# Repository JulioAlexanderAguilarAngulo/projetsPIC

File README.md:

projetsPIC
==========

Pic Microcontroller Based Projects

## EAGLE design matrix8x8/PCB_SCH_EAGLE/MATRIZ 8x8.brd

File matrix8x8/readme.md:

VIDEOS:
	https://www.youtube.com/watch?v=V3_yqs96JEo&index=2&list=PLWLQFv_oI8OCp_rWr5gJBbSe7xD8OUvFn

Project Overview:

	BETATESTERS (HW and SW) needed!!

Project Members:

    Hardware:  Pedro Sanchez
    
    Firmware:  Julio Aguilar
               Pedro Sanchez
               -more to come-	   
			   
Acknowledgements:

Tools:

	Software:  XC8 compiler +  MPLABX IDE
  
Code History

	V0.01a: Initial Dummy Code template and structured definitions
			- hardware target: Pedro Sanchez board (available as sch-brd)
	V0.01b: Spi-Like Shift Register Function Added inside main file
	V0.01c: Matrix Test initial Code.
	V0.01d: Scroll and Blink Test Code OK and Tested.  End of 0.01x release
			simulation and hardware test:
			https://www.youtube.com/watch?v=cb9j1CJo0fE
			https://www.youtube.com/watch?v=V3_yqs96JEo

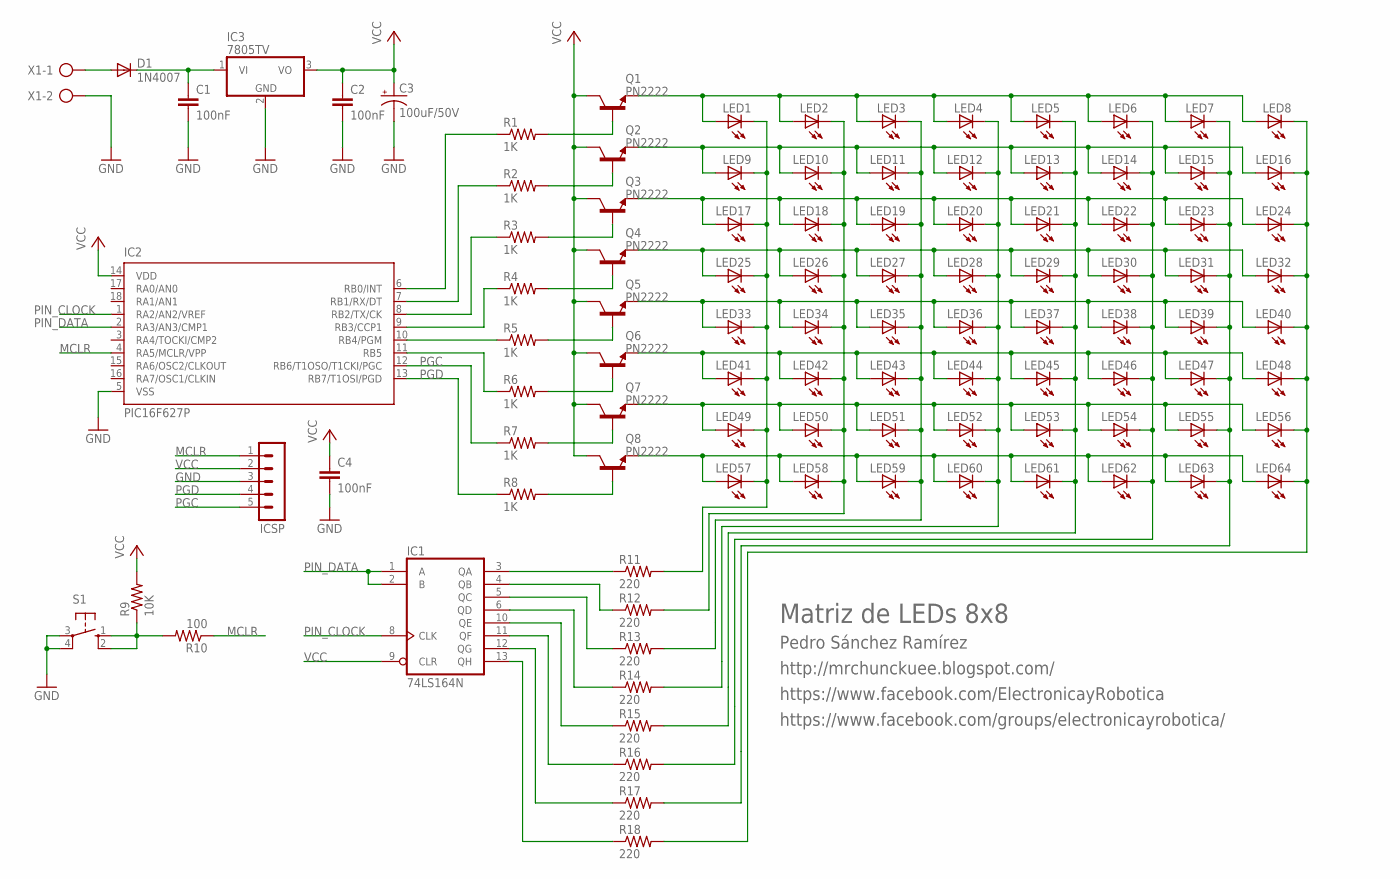
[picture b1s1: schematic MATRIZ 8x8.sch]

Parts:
C1, C2, C4: 100nF; C050-024X044
C3: 100uF/50V; E5-10,5
D1: 1N4007; DO41-10
IC1: 74LS164N; DIL14
IC2: PIC16F627P; DIL18
IC3: 7805TV; TO220V
ICSP: MA05-1
LED1, LED2, LED3, LED4, LED5, LED6, LED7, LED8, LED9, LED10, LED11, LED12, LED13, LED14, LED15, LED16, LED17, LED18, LED19, LED20, LED21, LED22, LED23, LED24, LED25, LED26, LED27, LED28, LED29, LED30, LED31, LED32, LED33, LED34, LED35, LED36, LED37, LED38, LED39, LED40, LED41, LED42, LED43, LED44, LED45, LED46, LED47, LED48, LED49, LED50, LED51, LED52, LED53, LED54, LED55, LED56, LED57, LED58, LED59, LED60, LED61, LED62, LED63, LED64: LED5MM
Q1, Q2, Q3, Q4, Q5, Q6, Q7, Q8: PN2222; TO92-EBC
R1, R2, R3, R4, R5, R6, R7, R8: 1K; 0204/7
R9: 10K; 0204/7
R10: 100; 0204/7
R11, R12, R13, R14, R15, R16, R17, R18: 220; 0204/7
S1: 10-XX; B3F-10XX
X1: AK500/2-H

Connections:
GND: C1.2, C2.2, C3.-, C4.2, IC1.7 (GND), IC2.5 (VSS), IC3.2 (GND), ICSP.3, S1.3, S1.4 (P1), X1.2
MCLR: IC2.4 (RA5/MCLR/VPP), ICSP.1, R10.1
unnamed: LED1.A, LED2.A, LED3.A, LED4.A, LED5.A, LED6.A, LED7.A, LED8.A, Q1.E
unnamed: LED57.A, LED58.A, LED59.A, LED60.A, LED61.A, LED62.A, LED63.A, LED64.A, Q8.E
unnamed: LED25.A, LED26.A, LED27.A, LED28.A, LED29.A, LED30.A, LED31.A, LED32.A, Q4.E
unnamed: LED9.A, LED10.A, LED11.A, LED12.A, LED13.A, LED14.A, LED15.A, LED16.A, Q2.E
unnamed: LED33.A, LED34.A, LED35.A, LED36.A, LED37.A, LED38.A, LED39.A, LED40.A, Q5.E
unnamed: LED49.A, LED50.A, LED51.A, LED52.A, LED53.A, LED54.A, LED55.A, LED56.A, Q7.E
unnamed: D1.A, X1.1
unnamed: LED17.A, LED18.A, LED19.A, LED20.A, LED21.A, LED22.A, LED23.A, LED24.A, Q3.E
unnamed: LED41.A, LED42.A, LED43.A, LED44.A, LED45.A, LED46.A, LED47.A, LED48.A, Q6.E
unnamed: Q1.B, R1.2
unnamed: Q8.B, R8.2
unnamed: Q7.B, R7.2
unnamed: Q6.B, R6.2
unnamed: Q5.B, R5.2
unnamed: Q4.B, R4.2
unnamed: Q2.B, R2.2
unnamed: Q3.B, R3.2
unnamed: IC2.8 (RB2/TX/CK), R3.1
unnamed: C1.1, D1.C, IC3.1 (VI)
unnamed: IC2.9 (RB3/CCP1), R4.1
unnamed: IC2.10 (RB4/PGM), R5.1
unnamed: IC2.7 (RB1/RX/DT), R2.1
unnamed: IC2.6 (RB0/INT), R1.1
unnamed: IC2.11 (RB5), R6.1
unnamed: R9.1, R10.2, S1.1 (S), S1.2 (S1)
unnamed: IC1.3 (QA), R11.1
unnamed: IC1.4 (QB), R12.1
unnamed: IC1.5 (QC), R13.1
unnamed: IC1.6 (QD), R14.1
unnamed: IC1.10 (QE), R15.1
unnamed: IC1.11 (QF), R16.1
unnamed: IC1.12 (QG), R17.1
unnamed: IC1.13 (QH), R18.1
PGC: IC2.12 (RB6/T1OSO/T1CKI/PGC), ICSP.5, R7.1
PGD: IC2.13 (RB7/T1OSI/PGD), ICSP.4, R8.1
PIN_CLOCK: IC1.8 (CLK), IC2.1 (RA2/AN2/VREF)
PIN_DATA: IC1.1 (A), IC1.2 (B), IC2.2 (RA3/AN3/CMP1)
QA: LED1.K (C), LED9.K (C), LED17.K (C), LED25.K (C), LED33.K (C), LED41.K (C), LED49.K (C), LED57.K (C), R11.2
QB: LED2.K (C), LED10.K (C), LED18.K (C), LED26.K (C), LED34.K (C), LED42.K (C), LED50.K (C), LED58.K (C), R12.2
QC: LED3.K (C), LED11.K (C), LED19.K (C), LED27.K (C), LED35.K (C), LED43.K (C), LED51.K (C), LED59.K (C), R13.2
QD: LED4.K (C), LED12.K (C), LED20.K (C), LED28.K (C), LED36.K (C), LED44.K (C), LED52.K (C), LED60.K (C), R14.2
QE: LED5.K (C), LED13.K (C), LED21.K (C), LED29.K (C), LED37.K (C), LED45.K (C), LED53.K (C), LED61.K (C), R15.2
QF: LED6.K (C), LED14.K (C), LED22.K (C), LED30.K (C), LED38.K (C), LED46.K (C), LED54.K (C), LED62.K (C), R16.2
QG: LED7.K (C), LED15.K (C), LED23.K (C), LED31.K (C), LED39.K (C), LED47.K (C), LED55.K (C), LED63.K (C), R17.2
QH: LED8.K (C), LED16.K (C), LED24.K (C), LED32.K (C), LED40.K (C), LED48.K (C), LED56.K (C), LED64.K (C), R18.2
VCC: C2.1, C3.+, C4.1, IC1.9 (CLR), IC1.14 (VCC), IC2.14 (VDD), IC3.3 (VO), ICSP.2, Q1.C, Q2.C, Q3.C, Q4.C, Q5.C, Q6.C, Q7.C, Q8.C, R9.2

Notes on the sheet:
Matriz de LEDs 8x8
Pedro Sánchez Ramírez
http://mrchunckuee.blogspot.com/
https://www.facebook.com/ElectronicayRobotica
https://www.facebook.com/groups/electronicayrobotica/

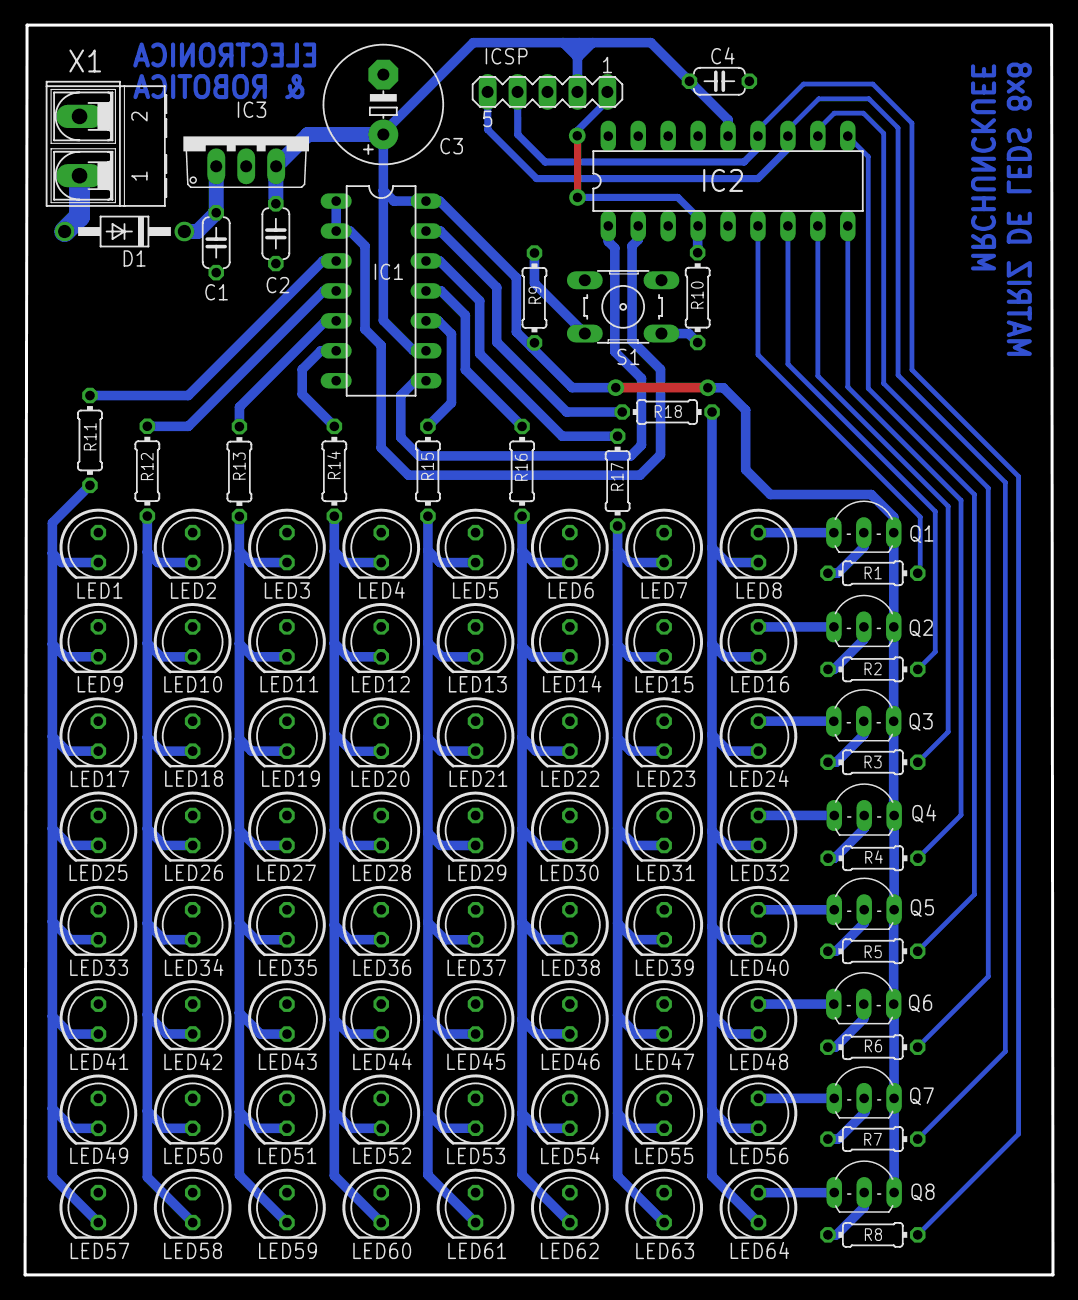
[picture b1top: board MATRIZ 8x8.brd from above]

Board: 2 copper layers, 87.2 x 106.0 mm, 101 parts (0 on the bottom side), 48 nets.

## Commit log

2014-08-29 PIC-based 8X8 LED animated sign
    PIC-based 8X8 LED animated sign:
    Collaborative project:
    Members (by now):
    Pedro Sanchez (Mexico)
    Julio Aguilar Angulo (Peru)
2014-08-29 Ver 0.01c submitted
    BETATESTERS (HW and SW) needed!!
    * History:
    *
    * V0.01a: Initial Dummy Code template and structured definitions
    * - hardware target: Pedro Sanchez board (available as
    sch-brd)
2014-08-29 minor global updates
    latest version : 0.01c
2014-08-29 ver 0.01d submitted
    Last 0.01 Scroll and mirror effect added
    submission, after this starts version 2
2014-08-30 description updated
    test videos added!!!
2014-09-01 Version 0.02a released
    Shift register now as a library-driver
    Modular Approach
2014-11-19 Create pic18Fstick
